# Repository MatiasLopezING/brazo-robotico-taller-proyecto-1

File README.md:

# Brazo robótico teleoperado de cinco servomotores

Proyecto grupal de **Taller de Proyecto I (E0306)** — Facultad de Ingeniería, UNLP
Departamento de Electrotecnia — 2.º cuatrimestre 2026

Brazo robótico de cuatro grados de libertad más pinza, accionado por cinco
servomotores y gobernado por la placa **EDU-CIAA-NXP** (microcontrolador NXP
LPC4337, ARM Cortex-M4), para la manipulación remota de recipientes en entornos
con riesgo químico, con monitoreo de gases y parada de emergencia por hardware.

## Integrantes

| Nombre | Legajo |
|---|---|
| Lopez Matias | 02670/0 |
| Juan David Alvarez | 03100/2 |
| Lautaro Lopes | 02978/9 |
| Ariana Magali Ariza | 02879/6 |

Grupo N.º 3 · Docente a cargo: Malena Crespi

## Estado del proyecto

| Entrega | Vencimiento | Estado |
|---|---|---|
| Informe inicial | 10/09/2026 | entregado |
| Informe de avance 1 (diseño alto nivel, esquemáticos) | 05/10/2026 | entregado |
| Informe de avance 2 (diseño bajo nivel, PCB) | 05/11/2026 | pendiente |
| Informe final | 11/02/2027 | pendiente |
| Presentación | 18 y 22/02/2027 | pendiente |

## Contenido

- `Informe_Inicial_v0.docx` — informe inicial, versión editable
- `Informe_Inicial_v0.pdf` — informe inicial, versión para entregar

A medida que avance el proyecto se sumarán el firmware, los esquemáticos, el
diseño de PCB y los protocolos de ensayo.

## Dimensiones del brazo

El brazo cuenta con **cuatro grados de libertad** (hombro, codo, muñeca y
pinza), accionado por cinco servomotores. Los primeros cálculos de
dimensionamiento —geometría de eslabones, par necesario en cada articulación
y selección de servos— se encuentran en el cuaderno
`Dimensionamiento_brazo.ipynb`.

Los valores obtenidos son preliminares; falta corrección y revisión en detalle.

## Convenciones de trabajo

- Rama `main`: siempre en estado entregable.
- Ramas de trabajo: `feature/<tema>`, `fix/<tema>`, `docs/<tema>`.
- Mensajes de commit: `<tipo>(<área>): <descripción en imperativo>`
  con tipos `feat | fix | docs | hw | test | chore` y áreas
  `firmware | hardware | mecanica | docs | ensayos`.
- Una etiqueta por entrega: `informe-inicial`, `avance-1`, `avance-2`, `final`.

## Documentación ampliada

Para información más detallada sobre el diseño, decisiones de arquitectura,
protocolo de comunicación y registro de avances, consultá la
**[Wiki del proyecto](https://github.com/MatiasLopezING/brazo-robotico-taller-proyecto-1/wiki)**.

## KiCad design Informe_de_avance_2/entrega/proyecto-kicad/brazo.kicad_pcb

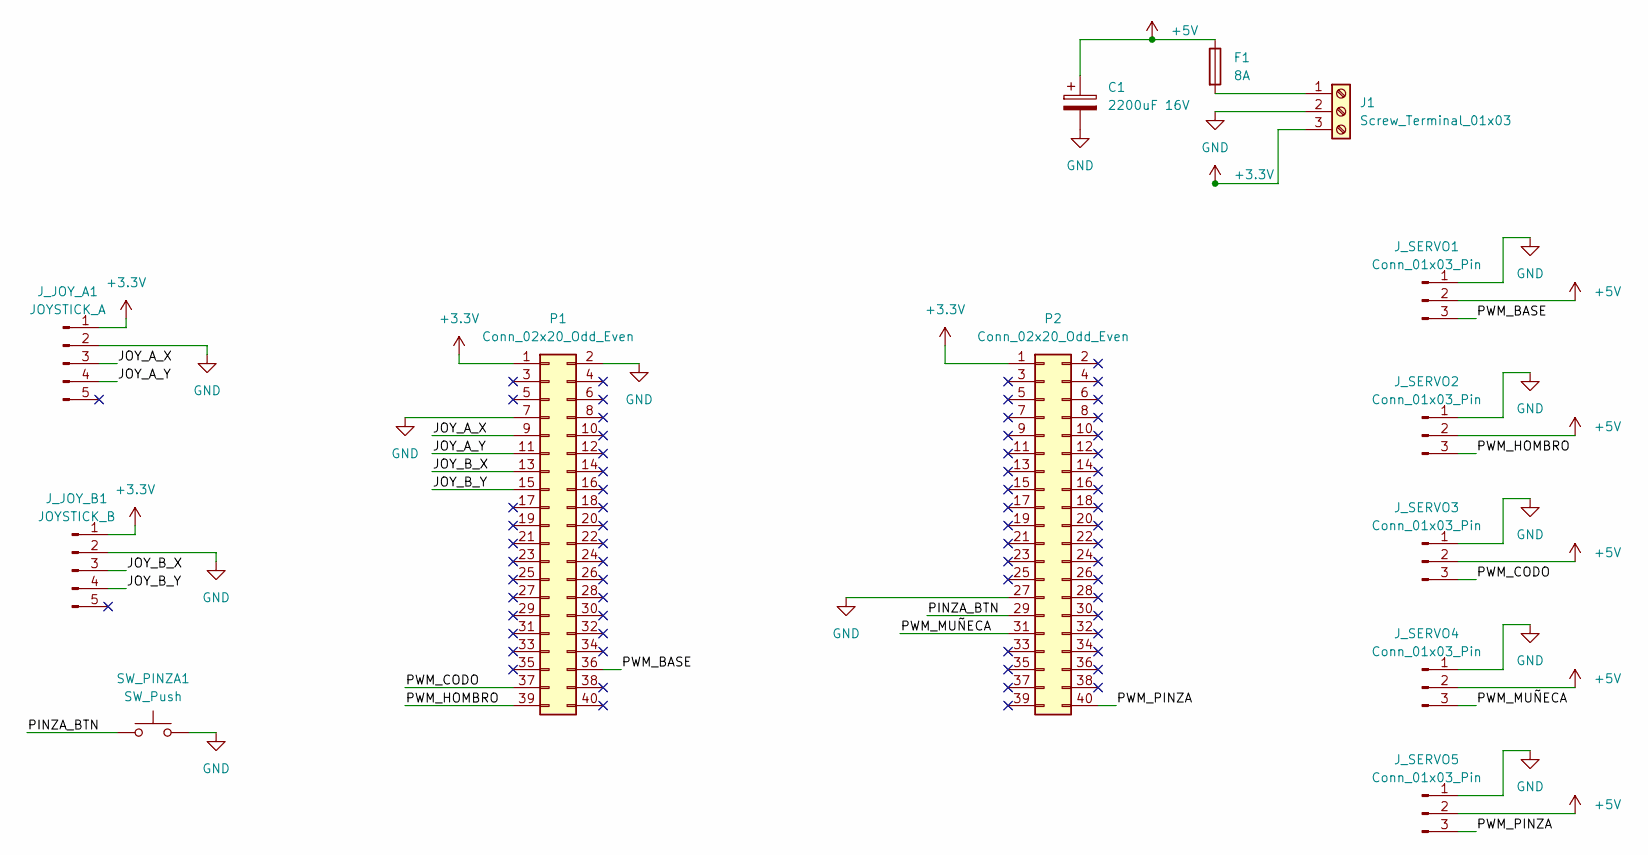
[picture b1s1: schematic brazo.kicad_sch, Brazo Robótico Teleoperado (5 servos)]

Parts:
C1: 2200uF 16V; CP_Radial_D12.5mm_P5.00mm
F1: 8A; PinSocket_1x02_P2.54mm_Vertical
J1: Screw_Terminal_01x03; TerminalBlock_Phoenix_MKDS-1,5-3-5.08_1x03_P5.08mm_Horizont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
J_JOY_A1: JOYSTICK_A; PinHeader_1x05_P2.54mm_Vertical
J_JOY_B1: JOYSTICK_B; PinHeader_1x05_P2.54mm_Vertical
J_SERVO1, J_SERVO2, J_SERVO3, J_SERVO4, J_SERVO5: Conn_01x03_Pin; PinHeader_1x03_P2.54mm_Vertical
P1, P2: Conn_02x20_Odd_Even; PinHeader_2x20_P2.54mm_Vertical
SW_PINZA1: SW_Push; PinHeader_1x02_P2.54mm_Vertical

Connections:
+3.3V: J1.3, J_JOY_A1.1, J_JOY_B1.1, P1.1, P2.1
+5V: C1.1, F1.1, J_SERVO1.2, J_SERVO2.2, J_SERVO3.2, J_SERVO4.2, J_SERVO5.2
/JOY_A_X: J_JOY_A1.3, P1.9
/JOY_A_Y: J_JOY_A1.4, P1.11
/JOY_B_X: J_JOY_B1.3, P1.13
/JOY_B_Y: J_JOY_B1.4, P1.15
/PINZA_BTN: P2.29, SW_PINZA1.1
/PWM_BASE: J_SERVO1.3, P1.36
/PWM_CODO: J_SERVO3.3, P1.37
/PWM_HOMBRO: J_SERVO2.3, P1.39
/PWM_MUÑECA: J_SERVO4.3, P2.31
/PWM_PINZA: J_SERVO5.3, P2.40
GND: C1.2, J1.2, J_JOY_A1.2, J_JOY_B1.2, J_SERVO1.1, J_SERVO2.1, J_SERVO3.1, J_SERVO4.1, J_SERVO5.1, P1.2, P1.7, P2.27, SW_PINZA1.2
unnamed: F1.2, J1.1

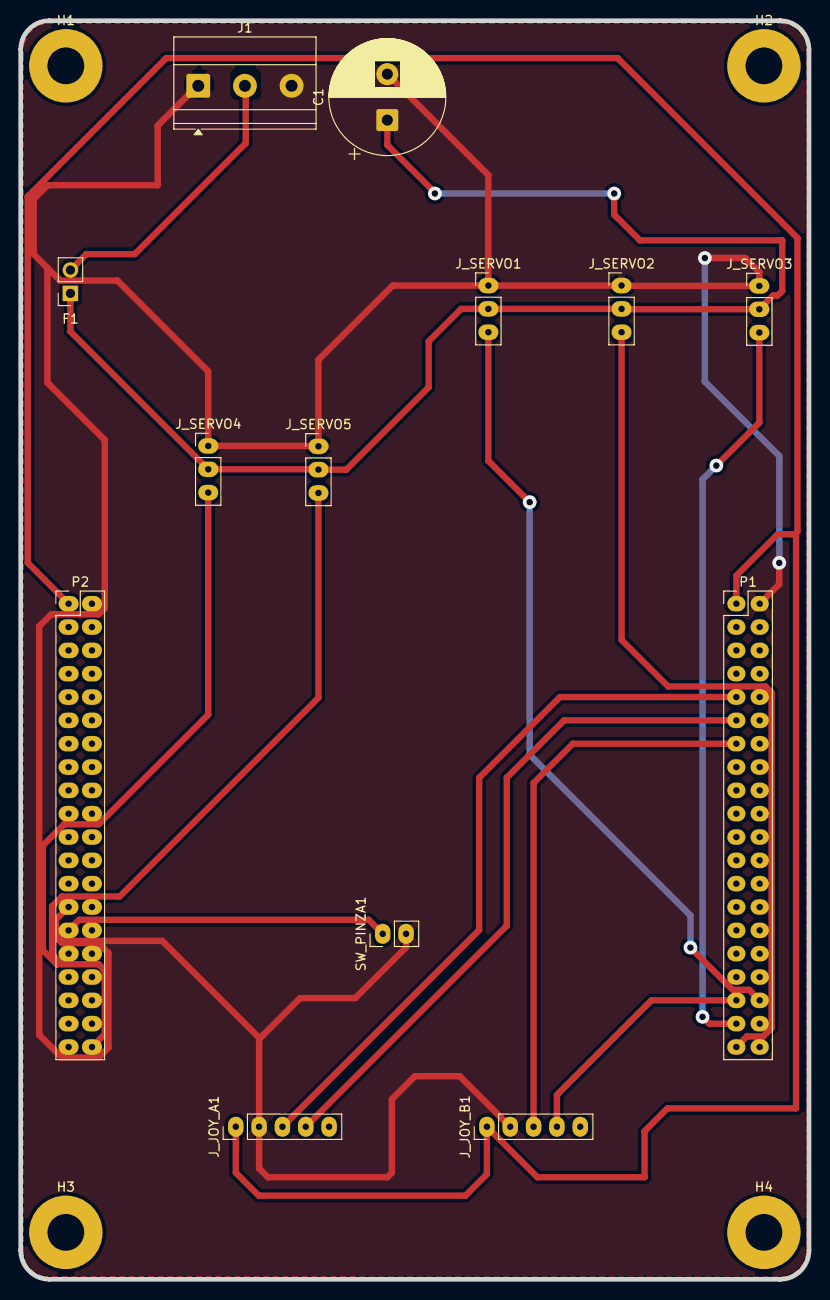
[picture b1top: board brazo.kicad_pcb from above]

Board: 2 copper layers, 85.8 x 137.0 mm, 17 parts (0 on the bottom side), 14 nets.

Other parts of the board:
H1, H2, H3, H4: MountingHole_4mm_Pad
